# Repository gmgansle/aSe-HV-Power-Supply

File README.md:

# aSe-HV-Power-Supply
This repository includes all of the production files, SOPs, design contraints, and all other important information regarding the High Voltage power supply for use with a Inter-Digitated Electrode-based amorphous Selenium photodetector, or any other semiconducter that can be read using the Cremat CR150 and CR11x Charge Sensitive Preamplifers.

Though the board in it's current state may look complete, it is not. You will need to connect multiple ground pads to their respective pours, amongst other things. Make sure to run a DRC that comes back clean before generating output files.

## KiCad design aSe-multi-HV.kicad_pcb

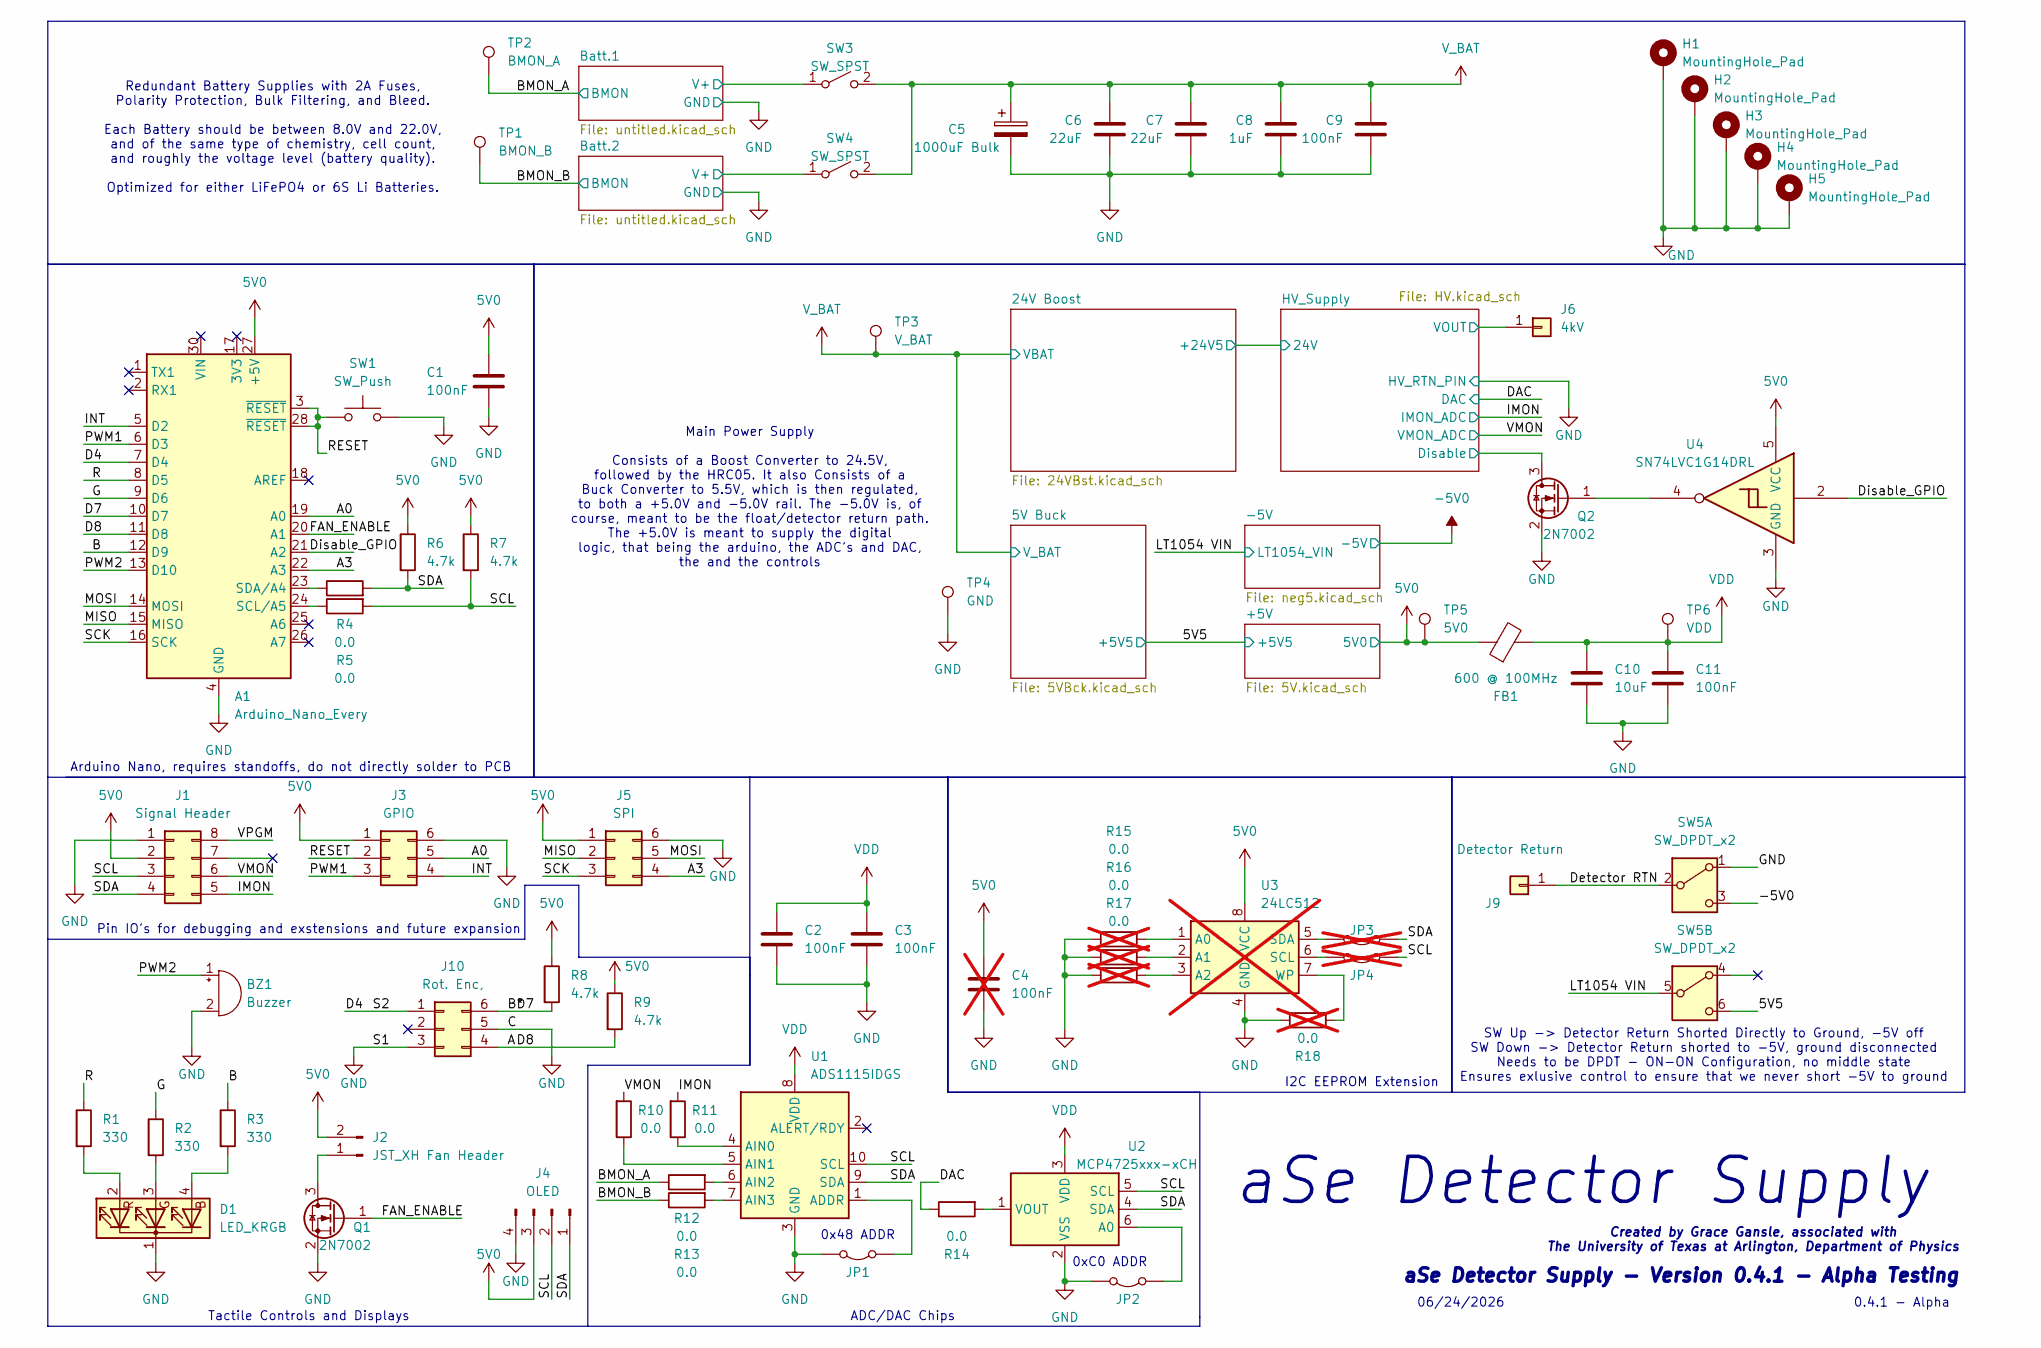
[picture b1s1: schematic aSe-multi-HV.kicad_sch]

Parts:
A1: Arduino_Nano_Every; Arduino_Nano
BZ1: Buzzer; PinSocket_1x02_P2.54mm_Vertical
C1, C2, C3, C9, C11: 100nF; C_1206_3216Metric_Pad1.33x1.80mm_HandSolder
C4: 100nF; C_1206_3216Metric_Pad1.33x1.80mm_HandSolder; not fitted
C5: 1000uF Bulk; CP_Radial_Tantal_D10.5mm_P5.00mm
C6, C7: 22uF; C_2220_5750Metric_Pad1.97x5.40mm_HandSolder
C8: 1uF; C_1206_3216Metric_Pad1.33x1.80mm_HandSolder
C10: 10uF; C_1206_3216Metric_Pad1.33x1.80mm_HandSolder
D1: LED_KRGB; PinSocket_2x02_P2.54mm_Vertical
FB1: 600 @ 100MHz; L_1206_3216Metric_Pad1.22x1.90mm_HandSolder
H1: MountingHole_Pad; MountingHole_2.2mm_M2_DIN965_Pad_TopBottom
H2, H3, H4, H5: MountingHole_Pad; MountingHole_2.2mm_M2_DIN965_Pad
J1: Signal Header; PinSocket_2x04_P2.54mm_Vertical
J2: JST_XH Fan Header; JST_XH_B2B-XH-AM_1x02_P2.50mm_Vertical
J3: GPIO; PinSocket_2x03_P2.54mm_Vertical
J4: OLED; PinSocket_1x04_P2.54mm_Vertical
J5: SPI; PinSocket_2x03_P2.54mm_Vertical
J6: 4kV; PinSocket_1x01_P2.54mm_Vertical
J9: Detector Return; PinSocket_1x01_P2.54mm_Vertical
J10: Rot. Enc,; PinSocket_2x03_P2.54mm_Vertical
JP1, JP2: SolderJumper-2_P1.3mm_Open_TrianglePad1.0x1.5mm
JP3, JP4: SolderJumper-2_P1.3mm_Open_TrianglePad1.0x1.5mm; not fitted
Q1, Q2: 2N7002; SOT-23
R1, R2, R3: 330; R_1206_3216Metric_Pad1.30x1.75mm_HandSolder
R4, R5, R10, R11, R12, R13, R14: 0.0; R_1206_3216Metric_Pad1.30x1.75mm_HandSolder
R6, R7, R8, R9: 4.7k; R_1206_3216Metric_Pad1.30x1.75mm_HandSolder
R15, R16, R17, R18: 0.0; R_1206_3216Metric_Pad1.30x1.75mm_HandSolder; not fitted
SW1: SW_Push; SW_PUSH_6mm_H5mm
SW3, SW4: SW_SPST; PinSocket_1x02_P2.54mm_Vertical
SW5: SW_DPDT_x2; PinSocket_2x03_P2.54mm_Vertical
TP1: BMON_B; TestPoint_Keystone_5000-5004_Miniature
TP2: BMON_A; TestPoint_Keystone_5000-5004_Miniature
TP3: V_BAT; TestPoint_Keystone_5000-5004_Miniature
TP4: GND; TestPoint_Keystone_5000-5004_Miniature
TP5: 5V0; TestPoint_Keystone_5000-5004_Miniature
TP6: VDD; TestPoint_Keystone_5000-5004_Miniature
U1: ADS1115IDGS; TSSOP-10_3x3mm_P0.5mm
U2: MCP4725xxx-xCH; SOT-23-6
U3: 24LC512; DIP-8_W7.62mm; not fitted
U4: SN74LVC1G14DRL; SOT-553

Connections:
5V0: A1.27 (+5V), C1.1, C4.1, FB1.1, J1.2, J2.2, J3.1, J4.3, J5.1, R6.1, R7.1, R8.1, R9.1, TP5.1 (1_1), U3.8 (VCC), U4.5 (VCC); also elsewhere on the board
-5V0: SW5.3 (C); also elsewhere on the board
/5V5: SW5.6 (C); also elsewhere on the board
/A: A1.11 (D8), J10.4, R9.2
/A0: A1.19 (A0), J3.5
/A3: A1.22 (A3), J5.4
/B: A1.12 (D9), R3.1
/B*: A1.10 (D7), J10.6, R8.2
/BMON_A: R12.1, TP2.1 (1_1); also elsewhere on the board
/BMON_B: R13.1, TP1.1 (1_1); also elsewhere on the board
/Batt.1/V+: SW3.1 (A); also elsewhere on the board
/Batt.2/V+: SW4.1 (A); also elsewhere on the board
/D4: A1.7 (D4), J10.1
/Detector RTN: J9.1 (Pin_1_1), SW5.2 (B)
/Disable_GPIO: A1.21 (A2), U4.2
/FAN_ENABLE: A1.20 (A1), Q1.1 (G)
/G: A1.9 (D6), R2.1
/HV_Supply/!Disable: Q2.3 (D); also elsewhere on the board
/HV_Supply/VOUT: J6.1 (Pin_1_1); also elsewhere on the board
/IMON: J1.5, R11.2; also elsewhere on the board
/INT: A1.5 (D2), J3.4
/LT1054 VIN: SW5.5 (B); also elsewhere on the board
/MISO: A1.15 (MISO), J5.2
/MOSI: A1.14 (MOSI), J5.5
/PWM1: A1.6 (D3), J3.3
/PWM2: A1.13 (D10), BZ1.1 (+)
/R: A1.8 (D5), R1.1
/RESET: A1.3 (~RESET), A1.28 (~RESET), J3.2, SW1.1
/SCK: A1.16 (SCK), J5.3
/SCL: J1.3, J4.2, JP4.1 (A), R5.2, R7.2, U1.10 (SCL), U2.5 (SCL)
/SDA: J1.4, J4.1, JP3.1 (A), R4.2, R6.2, U1.9 (SDA), U2.4 (SDA)
/VMON: J1.6, R10.2; also elsewhere on the board
/VPGM: J1.8, R14.1; also elsewhere on the board
GND: A1.4 (GND), A1.29 (GND), BZ1.2 (-), C1.2, C2.2, C3.2, C4.2, C5.2, C6.2, C7.2, C8.2, C9.2, C10.2, C11.2, D1.1 (K), H1.1 (1_1), H2.1 (1_1), H3.1 (1_1), H4.1 (1_1), H5.1 (1_1), J1.1, J3.6, J4.4, J5.6, J10.3, J10.5, JP1.2 (B), JP2.2 (B), Q1.2 (S), Q2.2 (S), R15.1, R16.1, R17.1, R18.2, SW1.2, SW5.1 (A), TP4.1 (1_1), U1.3 (GND), U2.2 (VSS), U3.4 (GND), U4.3 (GND); also elsewhere on the board
unnamed: A1.24 (SCL/A5), R5.1
unnamed: A1.23 (SDA/A4), R4.1
unnamed: D1.4 (BA), R3.2
unnamed: D1.3 (GA), R2.2
unnamed: D1.2 (RA), R1.2
unnamed: J2.1, Q1.3 (D)
unnamed: JP1.1 (A), U1.1 (ADDR)
unnamed: JP2.1 (A), U2.6 (A0)
unnamed: JP3.2 (B), U3.5 (SDA)
unnamed: JP4.2 (B), U3.6 (SCL)
unnamed: Q2.1 (G), U4.4
unnamed: R11.1, U1.4 (AIN0)
unnamed: R10.1, U1.5 (AIN1)
unnamed: R12.2, U1.6 (AIN2)
unnamed: R13.2, U1.7 (AIN3)
unnamed: R14.2, U2.1 (VOUT)
unnamed: R15.2, U3.1 (A0)
unnamed: R16.2, U3.2 (A1)
unnamed: R17.2, U3.3 (A2)
unnamed: R18.1, U3.7 (WP)
VDD: C2.1, C3.1, C10.1, C11.1, FB1.2, TP6.1 (1_1), U1.8 (VDD), U2.3 (VDD)
V_BAT: C5.1, C6.1, C7.1, C8.1, C9.1, SW3.2 (B), SW4.2 (B), TP3.1 (1_1); also elsewhere on the board

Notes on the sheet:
0x48 ADDR
0.4.1 - Alpha
SW Up -> Detector Return Shorted Directly to Ground, -5V off SW Down -> Detector Return shorted to -5V, ground disconnected Needs to be DPDT - ON-ON Configuration, no middle state Ensures exlusive control to ensure that we never short -5V to ground
Created by Grace Gansle, associated with The University of Texas at Arlington, Department of Physics
ADC/DAC Chips
aSe Detector Supply
Arduino Nano, requires standoffs, do not directly solder to PCB
0xC0 ADDR
Tactile Controls and Displays
06/24/2026
Redundant Battery Supplies with 2A Fuses, Polarity Protection, Bulk Filtering, and Bleed. Each Battery should be between 8.0V and 22.0V, and of the same type of chemistry, cell count, and roughly the voltage level (battery quality). Optimized for either LiFePO4 or 6S Li Batteries.
aSe Detector Supply - Version 0.4.1 - Alpha Testing
I2C EEPROM Extension
Pin IO's for debugging and exstensions and future expansion
Main Power Supply Consists of a Boost Converter to 24.5V, followed by the HRC05. It also Consists of a Buck Converter to 5.5V, which is then regulated, to both a +5.0V and -5.0V rail. The -5.0V is, of course, meant to be the float/detector return path. The +5.0V is meant to supply the digital logic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

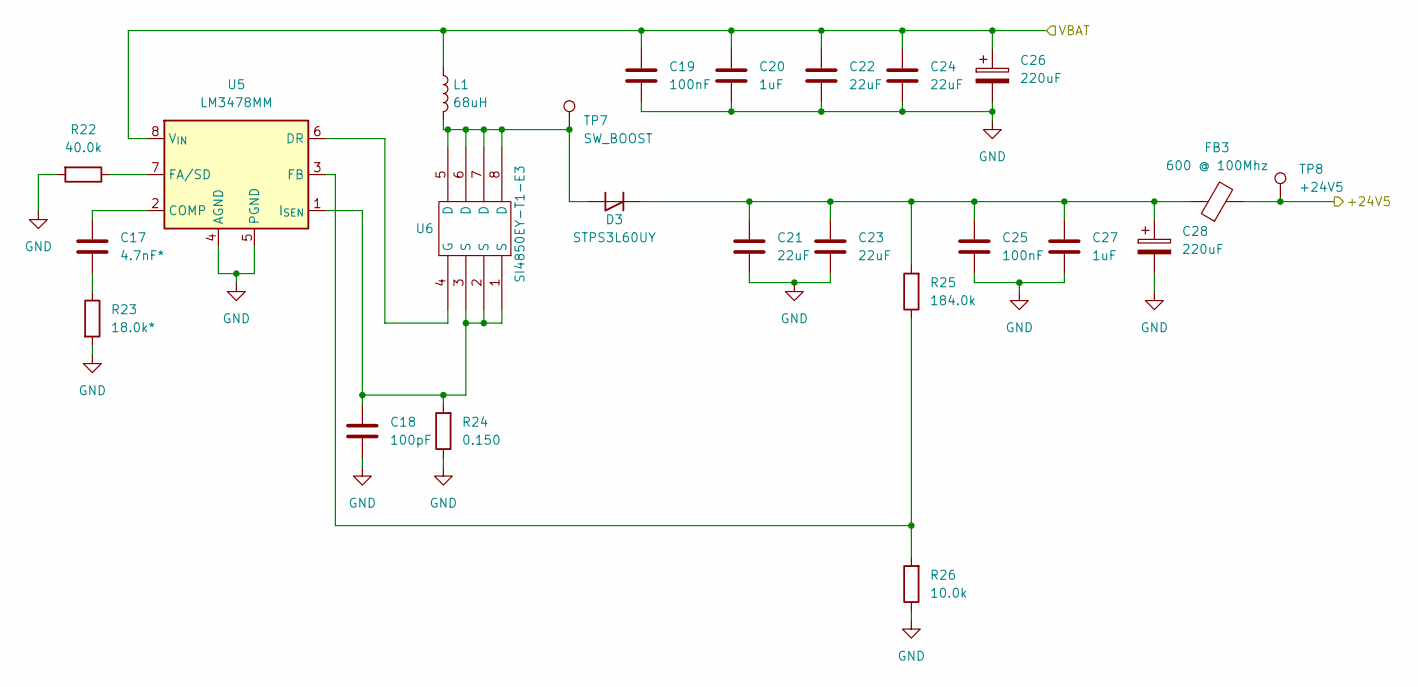
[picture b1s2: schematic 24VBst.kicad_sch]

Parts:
C17: 4.7nF*; C_1206_3216Metric_Pad1.33x1.80mm_HandSolder
C18: 100pF; C_1206_3216Metric_Pad1.33x1.80mm_HandSolder
C19, C25: 100nF; C_1206_3216Metric_Pad1.33x1.80mm_HandSolder
C20, C27: 1uF; C_1206_3216Metric_Pad1.33x1.80mm_HandSolder
C21, C22, C23, C24: 22uF; C_2220_5750Metric_Pad1.97x5.40mm_HandSolder
C26, C28: 220uF; CP_Radial_Tantal_D10.5mm_P5.00mm
D3: STPS3L60UY; D_SMB-SMC_Universal_Handsoldering
FB3: 600 @ 100Mhz; L_1206_3216Metric_Pad1.22x1.90mm_HandSolder
L1: 68uH; L_Coilcraft_MSS1260-XXX
R22: 40.0k; R_1206_3216Metric_Pad1.30x1.75mm_HandSolder
R23: 18.0k*; R_1206_3216Metric_Pad1.30x1.75mm_HandSolder
R24: 0.150; R_1206_3216Metric_Pad1.30x1.75mm_HandSolder
R25: 184.0k; R_1206_3216Metric_Pad1.30x1.75mm_HandSolder
R26: 10.0k; R_1206_3216Metric_Pad1.30x1.75mm_HandSolder
TP7: SW_BOOST; TestPoint_Keystone_5000-5004_Miniature
TP8: +24V5; TestPoint_Keystone_5000-5004_Miniature
U5: LM3478MM; VSSOP-8_3x3mm_P0.65mm
U6: SI4850EY-T1-E3; SOIC-8_3.9x4.9mm_P1.27mm

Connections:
/24V Boost/+24V5: FB3.2, TP8.1 (1_1); also elsewhere on the board
GND: C18.2, C19.2, C20.2, C21.2, C22.2, C23.2, C24.2, C25.2, C26.2, C27.2, C28.2, R22.2, R23.2, R24.1, R26.1, U5.4 (AGND), U5.5 (PGND); also elsewhere on the board
unnamed: C17.1, R23.1
unnamed: D3.2 (A), L1.2, TP7.1 (1_1), U6.5 (D), U6.6 (D), U6.7 (D), U6.8 (D)
unnamed: C21.1, C23.1, C25.1, C27.1, C28.1, D3.1 (K), FB3.1, R25.2
unnamed: C17.2, U5.2 (COMP)
unnamed: U5.6 (DR), U6.4 (G)
unnamed: R22.1, U5.7 (FA/SD)
unnamed: R25.1, R26.2, U5.3 (FB)
unnamed: C18.1, R24.2, U5.1 (I_{SEN}), U6.1 (S), U6.2 (S), U6.3 (S)
V_BAT: C19.1, C20.1, C22.1, C24.1, C26.1, L1.1, U5.8 (V_{IN}); also elsewhere on the board

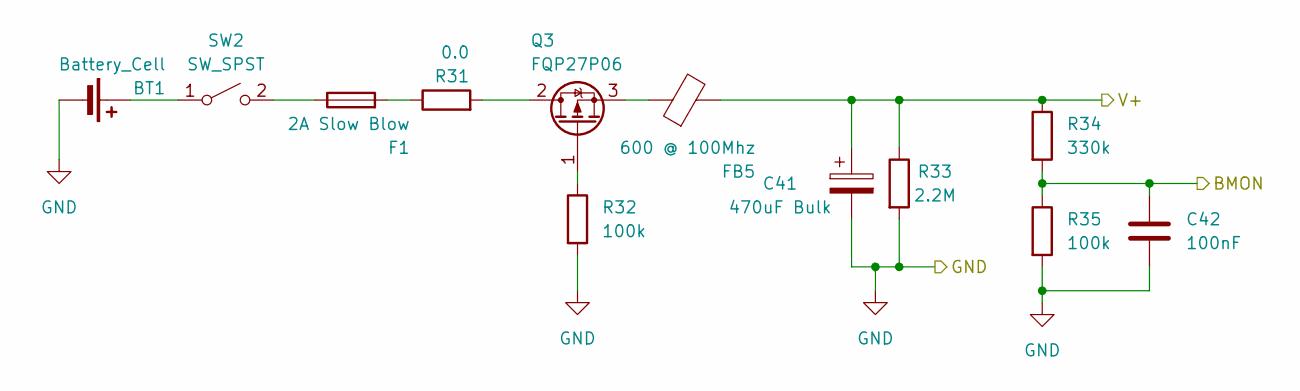
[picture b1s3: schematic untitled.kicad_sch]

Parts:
BT1: Battery_Cell; JST_XH_B2B-XH-AM_1x02_P2.50mm_Vertical
C41: 470uF Bulk; CP_Radial_Tantal_D10.5mm_P5.00mm
C42: 100nF; C_1206_3216Metric_Pad1.33x1.80mm_HandSolder
F1: 2A Slow Blow; Fuseholder_Littelfuse_100_series_5x20mm
FB5: 600 @ 100Mhz; L_1206_3216Metric_Pad1.22x1.90mm_HandSolder
Q3: FQP27P06; TO-220-3_Vertical
R31: 0.0; R_1206_3216Metric_Pad1.30x1.75mm_HandSolder
R32, R35: 100k; R_1206_3216Metric_Pad1.30x1.75mm_HandSolder
R33: 2.2M; R_1206_3216Metric_Pad1.30x1.75mm_HandSolder
R34: 330k; R_1206_3216Metric_Pad1.30x1.75mm_HandSolder
SW2: SW_SPST; PinSocket_1x02_P2.54mm_Vertical

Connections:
/BMON_B: C42.1, R34.2, R35.1; also elsewhere on the board
/Batt.2/V+: C41.1, FB5.2, R33.1, R34.1; also elsewhere on the board
GND: BT1.2 (-), C41.2, C42.2, R32.2, R33.2, R35.2; also elsewhere on the board
unnamed: BT1.1 (+), SW2.1 (A)
unnamed: F1.2, R31.1
unnamed: Q3.2 (D), R31.2
unnamed: Q3.1 (G), R32.1
unnamed: FB5.1, Q3.3 (S)
unnamed: F1.1, SW2.2 (B)

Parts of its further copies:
BT2: Battery_Cell; JST_XH_B2B-XH-AM_1x02_P2.50mm_Vertical
C58: 470uF Bulk; CP_Radial_Tantal_D10.5mm_P5.00mm
C59: 100nF; C_1206_3216Metric_Pad1.33x1.80mm_HandSolder
F2: 2A Slow Blow; Fuseholder_Littelfuse_100_series_5x20mm
FB7: 600 @ 100Mhz; L_1206_3216Metric_Pad1.22x1.90mm_HandSolder
Q4: FQP27P06; TO-220-3_Vertical
R36: 0.0; R_1206_3216Metric_Pad1.30x1.75mm_HandSolder
R37, R40: 100k; R_1206_3216Metric_Pad1.30x1.75mm_HandSolder
R38: 2.2M; R_1206_3216Metric_Pad1.30x1.75mm_HandSolder
R39: 330k; R_1206_3216Metric_Pad1.30x1.75mm_HandSolder
SW6: SW_SPST; PinSocket_1x02_P2.54mm_Vertical

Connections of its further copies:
/BMON_A: C59.1, R39.2, R40.1; also elsewhere on the board
/Batt.1/V+: C58.1, FB7.2, R38.1, R39.1; also elsewhere on the board
GND: BT2.2 (-), C58.2, C59.2, R37.2, R38.2, R40.2; also elsewhere on the board
unnamed: BT2.1 (+), SW6.1 (A)
unnamed: F2.2, R36.1
unnamed: Q4.2 (D), R36.2
unnamed: Q4.1 (G), R37.1
unnamed: FB7.1, Q4.3 (S)
unnamed: F2.1, SW6.2 (B)

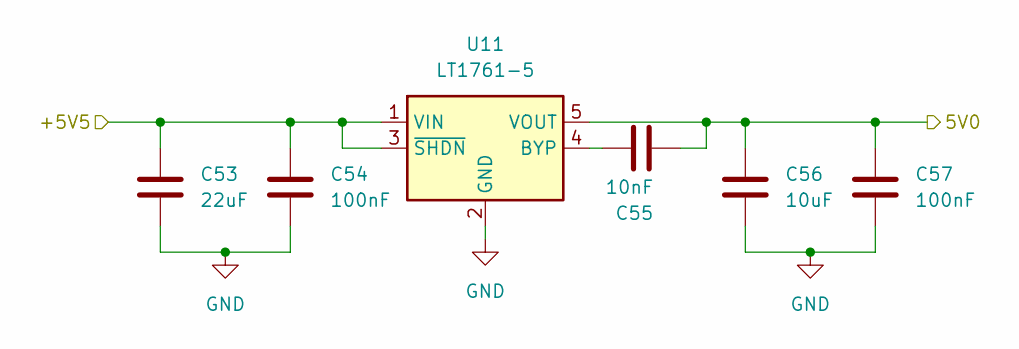
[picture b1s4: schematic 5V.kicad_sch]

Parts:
C53: 22uF; C_2220_5750Metric_Pad1.97x5.40mm_HandSolder
C54, C57: 100nF; C_1206_3216Metric_Pad1.33x1.80mm_HandSolder
C55: 10nF; C_1206_3216Metric_Pad1.33x1.80mm_HandSolder
C56: 10uF; C_2220_5750Metric_Pad1.97x5.40mm_HandSolder
U11: LT1761-5; TSOT-23-5

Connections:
5V0: C55.2, C56.1, C57.1, U11.5 (VOUT); also elsewhere on the board
/5V5: C53.1, C54.1, U11.1 (VIN), U11.3 (~SHDN); also elsewhere on the board
GND: C53.2, C54.2, C56.2, C57.2, U11.2 (GND); also elsewhere on the board
unnamed: C55.1, U11.4 (BYP)

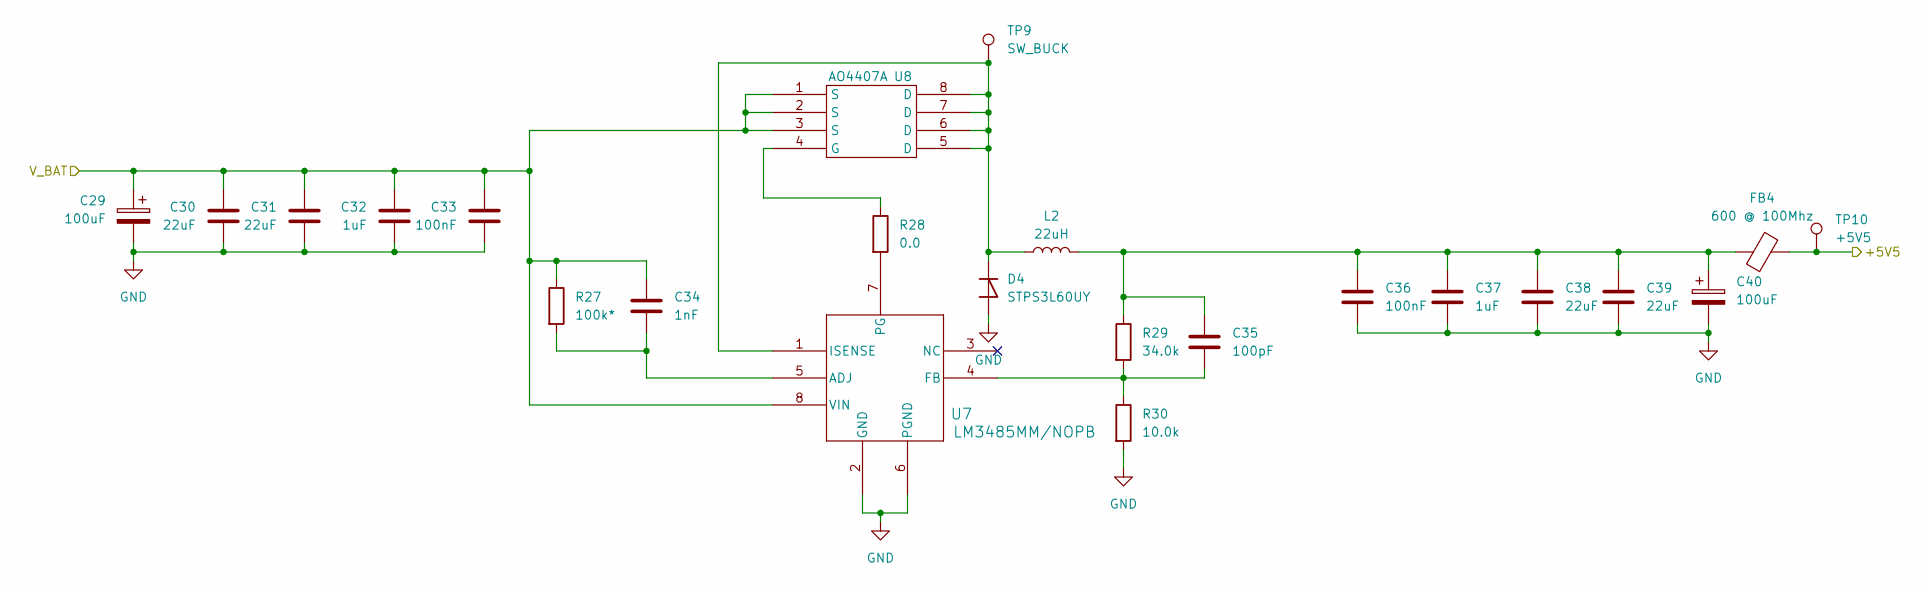
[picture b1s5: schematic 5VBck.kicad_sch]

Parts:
C29, C40: 100uF; CP_Radial_Tantal_D10.5mm_P5.00mm
C30, C31, C38, C39: 22uF; C_2220_5750Metric_Pad1.97x5.40mm_HandSolder
C32, C37: 1uF; C_1206_3216Metric_Pad1.33x1.80mm_HandSolder
C33, C36: 100nF; C_1206_3216Metric_Pad1.33x1.80mm_HandSolder
C34: 1nF; C_1206_3216Metric_Pad1.33x1.80mm_HandSolder
C35: 100pF; C_1206_3216Metric_Pad1.33x1.80mm_HandSolder
D4: STPS3L60UY; D_SMB-SMC_Universal_Handsoldering
FB4: 600 @ 100Mhz; L_1206_3216Metric_Pad1.22x1.90mm_HandSolder
L2: 22uH; L_Coilcraft_MSS1260-XXX
R27: 100k*; R_1206_3216Metric_Pad1.30x1.75mm_HandSolder
R28: 0.0; R_1206_3216Metric_Pad1.30x1.75mm_HandSolder
R29: 34.0k; R_1206_3216Metric_Pad1.30x1.75mm_HandSolder
R30: 10.0k; R_1206_3216Metric_Pad1.30x1.75mm_HandSolder
TP9: SW_BUCK; TestPoint_Keystone_5000-5004_Miniature
TP10: +5V5; TestPoint_Keystone_5000-5004_Miniature
U7: LM3485MM/NOPB; VSSOP-8_3x3mm_P0.65mm
U8: AO4407A; SOIC-8_3.9x4.9mm_P1.27mm

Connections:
/5V5: FB4.2, TP10.1 (1_1); also elsewhere on the board
GND: C29.2, C30.2, C31.2, C32.2, C33.2, C36.2, C37.2, C38.2, C39.2, C40.2, D4.2 (A), R30.2, U7.2 (GND), U7.6 (PGND); also elsewhere on the board
unnamed: C35.1, C36.1, C37.1, C38.1, C39.1, C40.1, FB4.1, L2.2, R29.1
unnamed: D4.1 (K), L2.1, TP9.1 (1_1), U7.1 (ISENSE), U8.5 (D), U8.6 (D), U8.7 (D), U8.8 (D)
unnamed: C34.2, R27.2, U7.5 (ADJ)
unnamed: C35.2, R29.2, R30.1, U7.4 (FB)
unnamed: R28.2, U7.7 (PG)
unnamed: R28.1, U8.4 (G)
V_BAT: C29.1, C30.1, C31.1, C32.1, C33.1, C34.1, R27.1, U7.8 (VIN), U8.1 (S), U8.2 (S), U8.3 (S); also elsewhere on the board

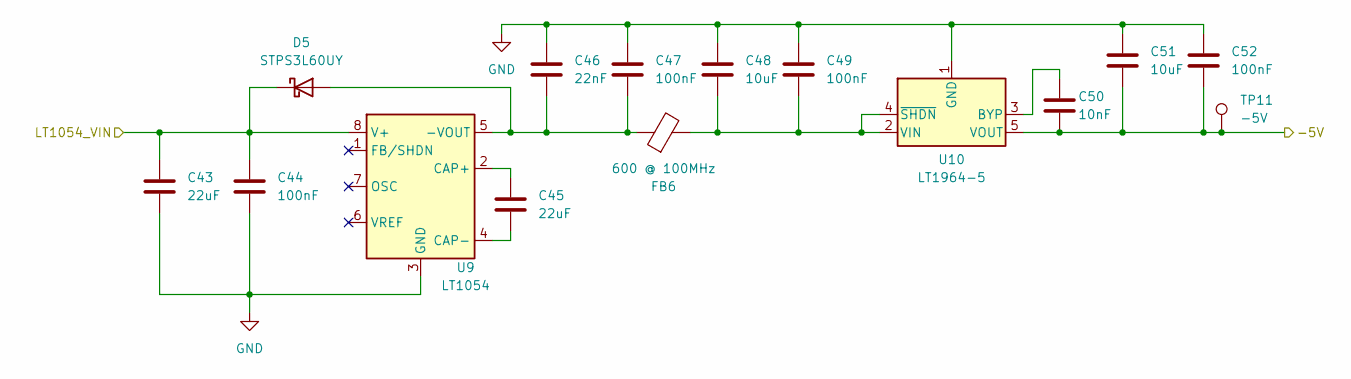
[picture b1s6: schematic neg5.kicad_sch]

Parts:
C43, C45: 22uF; C_2220_5750Metric_Pad1.97x5.40mm_HandSolder
C44, C47, C49, C52: 100nF; C_1206_3216Metric_Pad1.33x1.80mm_HandSolder
C46: 22nF; C_1206_3216Metric_Pad1.33x1.80mm_HandSolder
C48, C51: 10uF; C_2220_5750Metric_Pad1.97x5.40mm_HandSolder
C50: 10nF; C_1206_3216Metric_Pad1.33x1.80mm_HandSolder
D5: STPS3L60UY; D_SMB-SMC_Universal_Handsoldering
FB6: 600 @ 100MHz; L_1206_3216Metric_Pad1.22x1.90mm_HandSolder
TP11: -5V; TestPoint_Keystone_5000-5004_Miniature
U9: LT1054; DIP-8_W7.62mm_Socket
U10: LT1964-5; TSOT-23-5

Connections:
-5V0: C50.2, C51.2, C52.2, TP11.1 (1_1), U10.5 (VOUT); also elsewhere on the board
/LT1054 VIN: C43.1, C44.1, D5.1 (K), U9.8 (V+); also elsewhere on the board
GND: C43.2, C44.2, C46.1, C47.1, C48.1, C49.1, C51.1, C52.1, U9.3 (GND), U10.1 (GND); also elsewhere on the board
unnamed: C46.2, C47.2, D5.2 (A), FB6.1, U9.5 (-VOUT)
unnamed: C45.1, U9.2 (CAP+)
unnamed: C45.2, U9.4 (CAP-)
unnamed: C50.1, U10.3 (BYP)
unnamed: C48.2, C49.2, FB6.2, U10.2 (VIN), U10.4 (~SHDN)

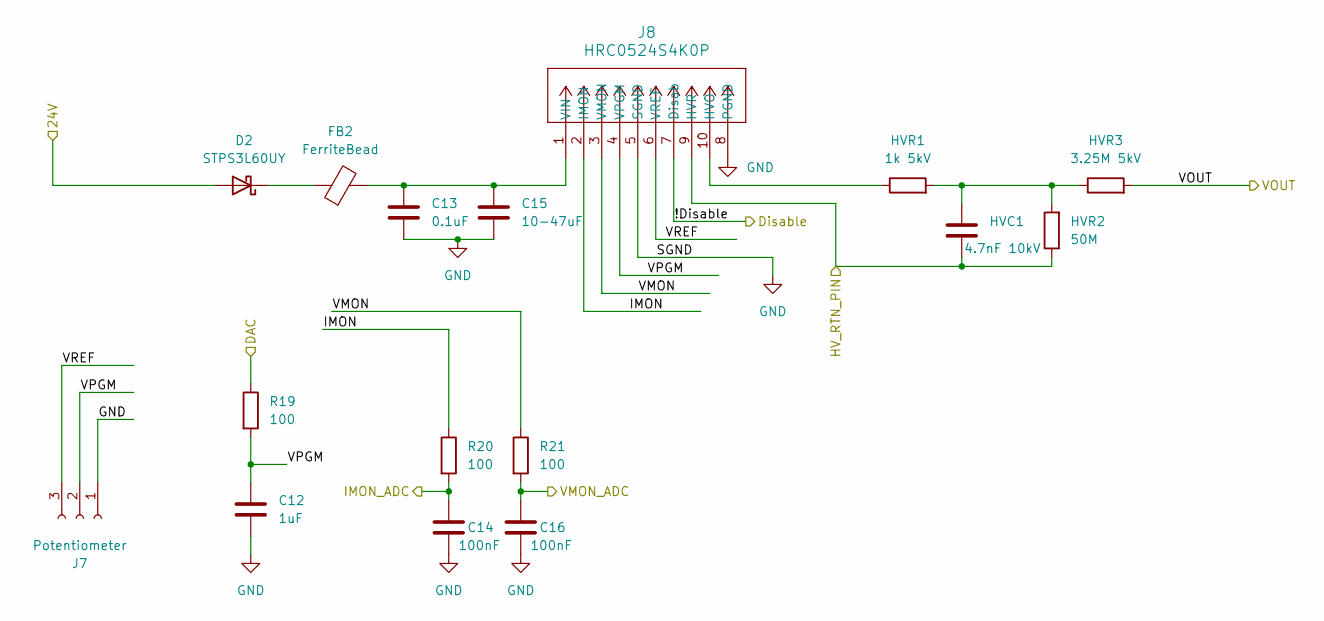
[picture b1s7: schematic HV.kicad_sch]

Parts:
C12: 1uF; C_1206_3216Metric_Pad1.33x1.80mm_HandSolder
C13: 0.1uF; C_1206_3216Metric_Pad1.33x1.80mm_HandSolder
C14, C16: 100nF; C_1206_3216Metric_Pad1.33x1.80mm_HandSolder
C15: 10-47uF; C_1206_3216Metric_Pad1.33x1.80mm_HandSolder
D2: STPS3L60UY; D_SMB-SMC_Universal_Handsoldering
FB2: FerriteBead; L_1206_3216Metric_Pad1.22x1.90mm_HandSolder
HVC1: 4.7nF 10kV; C_Disc_D16.0mm_W5.0mm_P10.00mm
HVR1: 1k 5kV; R_Axial_DIN0207_L6.3mm_D2.5mm_P15.24mm_Horizontal
HVR2: 50M; R_Axial_DIN0207_L6.3mm_D2.5mm_P15.24mm_Horizontal
HVR3: 3.25M 5kV; R_Axial_DIN0207_L6.3mm_D2.5mm_P15.24mm_Horizontal
J7: Potentiometer; PinSocket_1x03_P2.54mm_Vertical
J8: HRC0524S4K0P; CONN10_4S4K0N_XPP
R19, R20, R21: 100; R_1206_3216Metric_Pad1.30x1.75mm_HandSolder

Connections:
/24V Boost/+24V5: D2.2 (A); also elsewhere on the board
/HV_Supply/!Disable: J8.7 (Disab); also elsewhere on the board
/HV_Supply/IMON: J8.2 (IMON), R20.1
/HV_Supply/VMON: J8.3 (VMON), R21.1
/HV_Supply/VOUT: HVR3.2; also elsewhere on the board
/HV_Supply/VPGM: C12.1, J7.2, J8.4 (VPGM), R19.2
/HV_Supply/VREF: J7.3, J8.6 (VREF)
/IMON: C14.1, R20.2; also elsewhere on the board
/VMON: C16.1, R21.2; also elsewhere on the board
/VPGM: R19.1; also elsewhere on the board
GND: C12.2, C13.2, C14.2, C15.2, C16.2, HVC1.2, HVR2.1, J7.1, J8.5 (SGND), J8.8 (PGND), J8.9 (HVR); also elsewhere on the board
unnamed: D2.1 (K), FB2.1
unnamed: HVC1.1, HVR1.2, HVR2.2, HVR3.1
unnamed: HVR1.1, J8.10 (HVO)
unnamed: C13.1, C15.1, FB2.2, J8.1 (VIN)

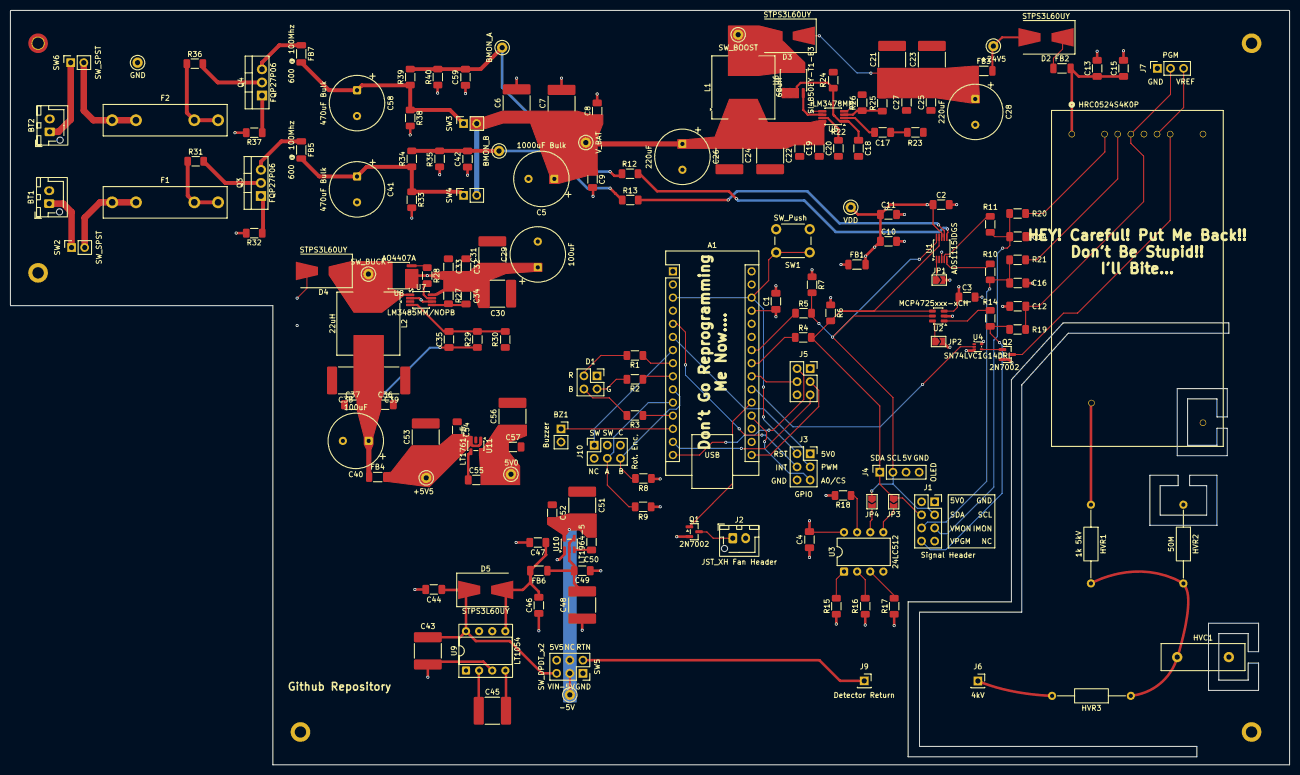
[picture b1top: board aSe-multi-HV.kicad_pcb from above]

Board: 4 copper layers, 247.5 x 145.9 mm, 174 parts (0 on the bottom side), 97 nets.
